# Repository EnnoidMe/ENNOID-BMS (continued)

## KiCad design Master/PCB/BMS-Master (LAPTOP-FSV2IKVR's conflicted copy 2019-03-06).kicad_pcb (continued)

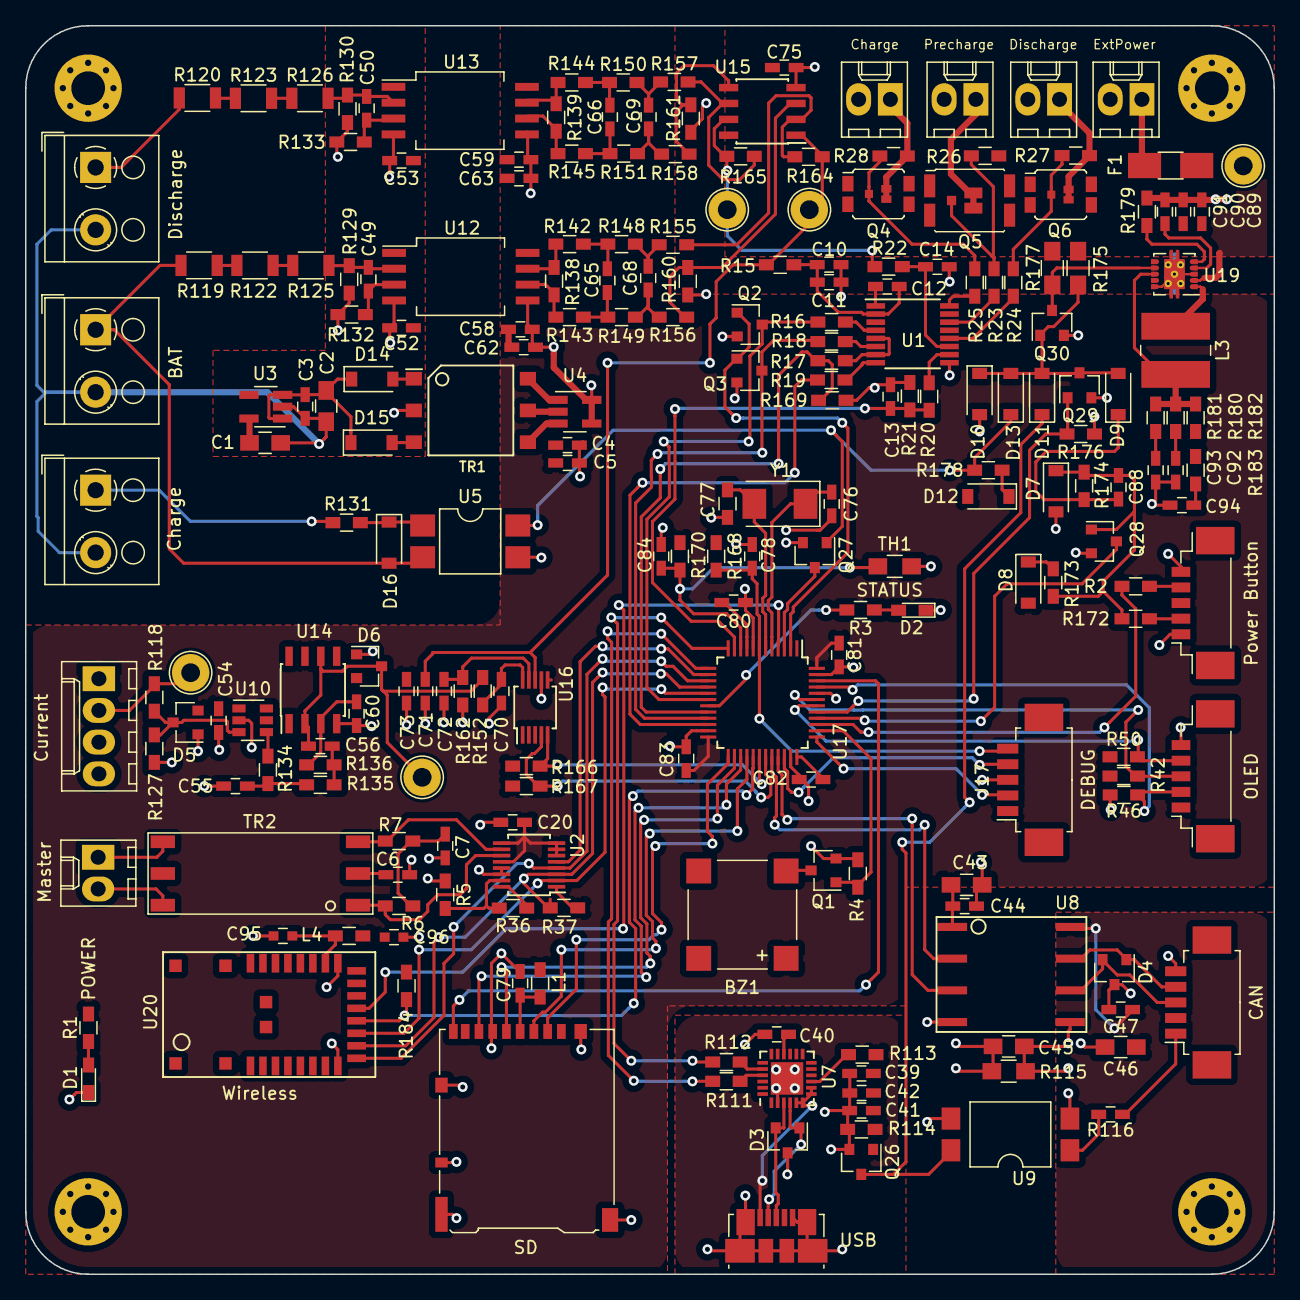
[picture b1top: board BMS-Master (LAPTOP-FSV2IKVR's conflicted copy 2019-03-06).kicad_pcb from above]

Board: 2 copper layers, 100.0 x 100.0 mm, 225 parts (1 on the bottom side), 148 nets.

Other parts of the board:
C10, C11, C14: 10n; C_0603_HandSoldering
C12: 2.2u; C_0603_HandSoldering
C13: 100n; C_0603_HandSoldering
C95, C96: 2.2u; C_0603
L4: BLM18PG330SN1D; L_0603_HandSoldering
Q4, Q6: IRF6614; DirectFET_ST
Q5: IRF9383M; DirectFET_MX
R15, R22: 100; R_0603_HandSoldering
R16, R17, R18, R19: 10k; R_0603_HandSoldering
R20: 33k; R_0603_HandSoldering
R21: 2.2k; R_0603_HandSoldering
R26: 4.7M; R_0603_HandSoldering
R184: 4.75k; R_0603_HandSoldering
U1: BQ76200; TSSOP-16_4.4x5mm_Pitch0.65mm
U20: A1101R09C00GM; A1101R09C

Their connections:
/MCU/MISO: U20.10; also elsewhere on the board
/MCU/MOSI: U20.11; also elsewhere on the board
/MCU/PreChargeEnable: R19.1; also elsewhere on the board
/MCU/SCK: U20.9; also elsewhere on the board
/MCU/SPI_WT_SS: R184.2, U20.12; also elsewhere on the board
/MCU/VoutSense: C13.2, R20.2, R21.1; also elsewhere on the board
/PowerMonitor/24V: Q4.1, Q5.1, Q6.1, R26.1; also elsewhere on the board
/PowerMonitor/Vbat: R15.1; also elsewhere on the board
/PowerMonitor/Vpack: R22.2; also elsewhere on the board
/switches/Charge: Q4.3; also elsewhere on the board
/switches/Discharge: Q6.3; also elsewhere on the board
/switches/Enable: R17.1; also elsewhere on the board
/switches/Precharge: Q5.3; also elsewhere on the board
/wireless/GDO0: U20.13; also elsewhere on the board
GND: C10.1, C11.1, C13.1, C14.1, C95.2, C96.2, R21.2, U1.9, U20.8, U20.17; also elsewhere on the board
unnamed: C10.2, C11.2, C12.2, R15.2, U1.2
unnamed: C12.1, U1.1
unnamed: C14.2, R22.1, U1.11
unnamed: C95.1, L4.1, U20.18
unnamed 115: Q4.2; also elsewhere on the board
unnamed 116: Q5.2, R26.2; also elsewhere on the board
unnamed 117: Q6.2; also elsewhere on the board
unnamed: R16.2, U1.4
unnamed: R17.2, U1.5, U1.7
unnamed: R18.2, U1.6
unnamed: R19.2, U1.8
unnamed: R20.1, U1.10
unnamed 127: U1.12; also elsewhere on the board
